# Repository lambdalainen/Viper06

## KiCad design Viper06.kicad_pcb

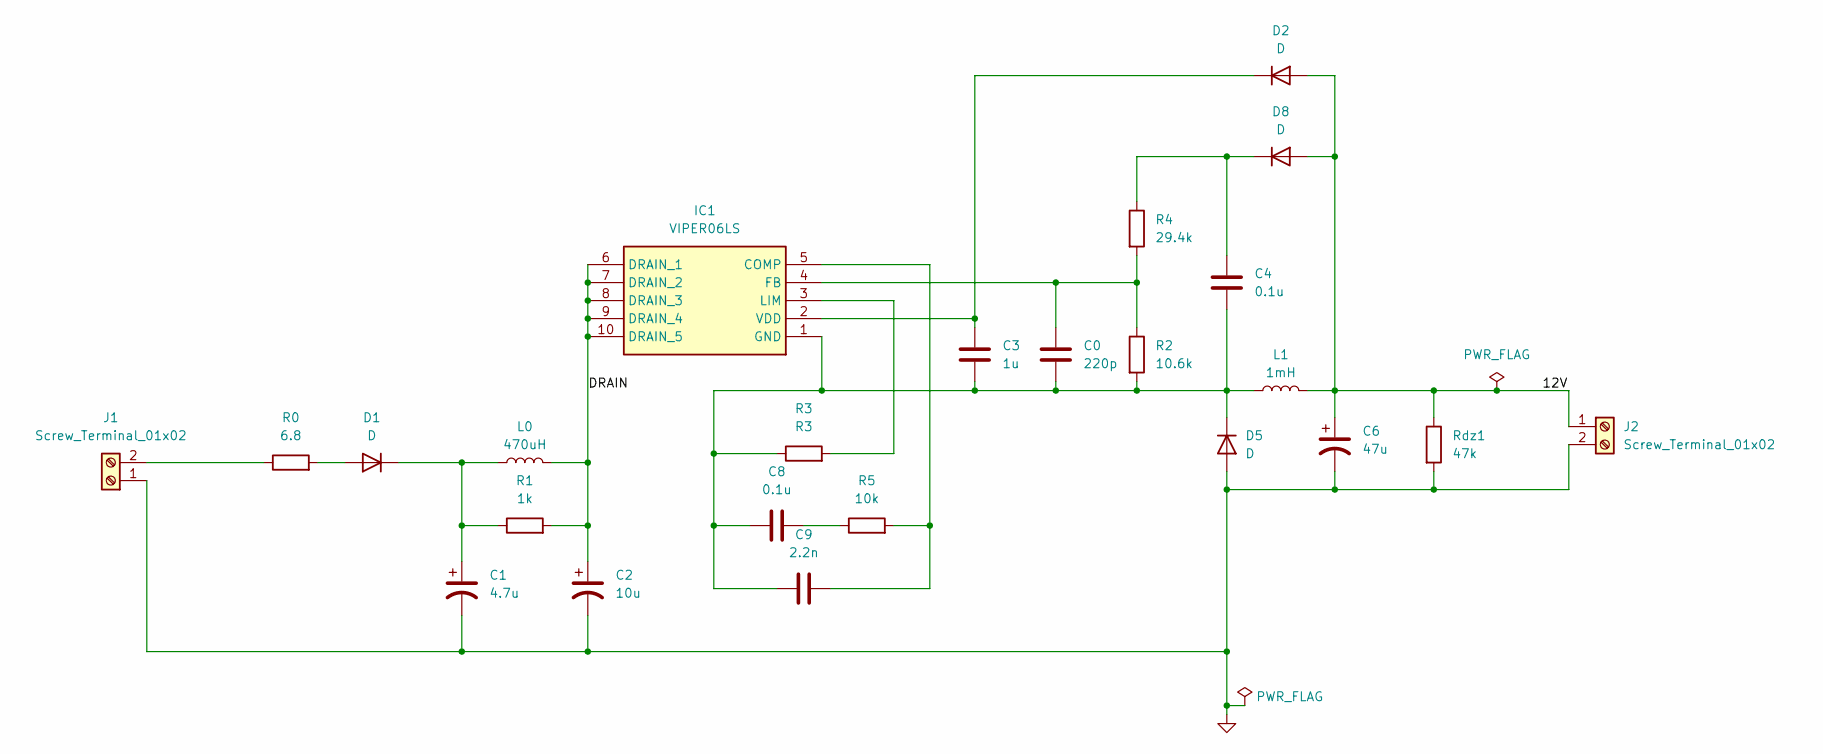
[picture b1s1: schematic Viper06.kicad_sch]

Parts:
C0: 220p; C_0603_1608Metric
C1: 4.7u; CP_Radial_D8.0mm_P3.50mm
C2: 10u; CP_Radial_D10.0mm_P5.00mm
C3: 1u; C_1206_3216Metric
C4, C8: 0.1u; C_0805_2012Metric
C6: 47u; CP_Radial_D6.3mm_P2.50mm
C9: 2.2n; C_0603_1608Metric
D1, D2: D; DIOM5127X229N
D5: D; DIOM5126X265N
D8: D; D_SMA
IC1: VIPER06LS; SOP100P600X175-10N; Manufacturer_Part_Number VIPER06LS; Mouser Part Number 511-VIPER06LS
J1, J2: Screw_Terminal_01x02; TerminalBlock_Phoenix_PT-1,5-2-3.5-H_1x02_P3.50mm_Horizontal
L0: 470uH; L_Axial_L13.0mm_D4.5mm_P5.08mm_Vertical_Fastron_HCCC
L1: 1mH; L_Radial_D7.8mm_P5.00mm_Fastron_07HCP
R0: 6.8; R_Axial_DIN0207_L6.3mm_D2.5mm_P10.16mm_Horizontal
R1: 1k; R_0805_2012Metric
R2: 10.6k; R_0805_2012Metric
R3: R3; R_Axial_DIN0207_L6.3mm_D2.5mm_P10.16mm_Horizontal
R4: 29.4k; R_0805_2012Metric
R5: 10k; R_0805_2012Metric
Rdz1: 47k; R_0805_2012Metric

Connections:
/12V: C6.1, D2.2 (A), D8.2 (A), J2.1, L1.2, Rdz1.1
/DRAIN: C2.1, IC1.6 (DRAIN_1), IC1.7 (DRAIN_2), IC1.8 (DRAIN_3), IC1.9 (DRAIN_4), IC1.10 (DRAIN_5), L0.2, R1.2
GND: C1.2, C2.2, C6.2, D5.2 (A), J1.1, J2.2, Rdz1.2
unnamed: C8.2, R5.1
unnamed: D1.2 (A), R0.2
unnamed: C1.1, D1.1 (K), L0.1, R1.1
unnamed: C3.1, D2.1 (K), IC1.2 (VDD)
unnamed: C0.2, C3.2, C4.2, C8.1, C9.1, D5.1 (K), IC1.1 (GND), L1.1, R2.2, R3.1
unnamed: C4.1, D8.1 (K), R4.1
unnamed: C9.2, IC1.5 (COMP), R5.2
unnamed: C0.1, IC1.4 (FB), R2.1, R4.2
unnamed: IC1.3 (LIM), R3.2
unnamed: J1.2, R0.1

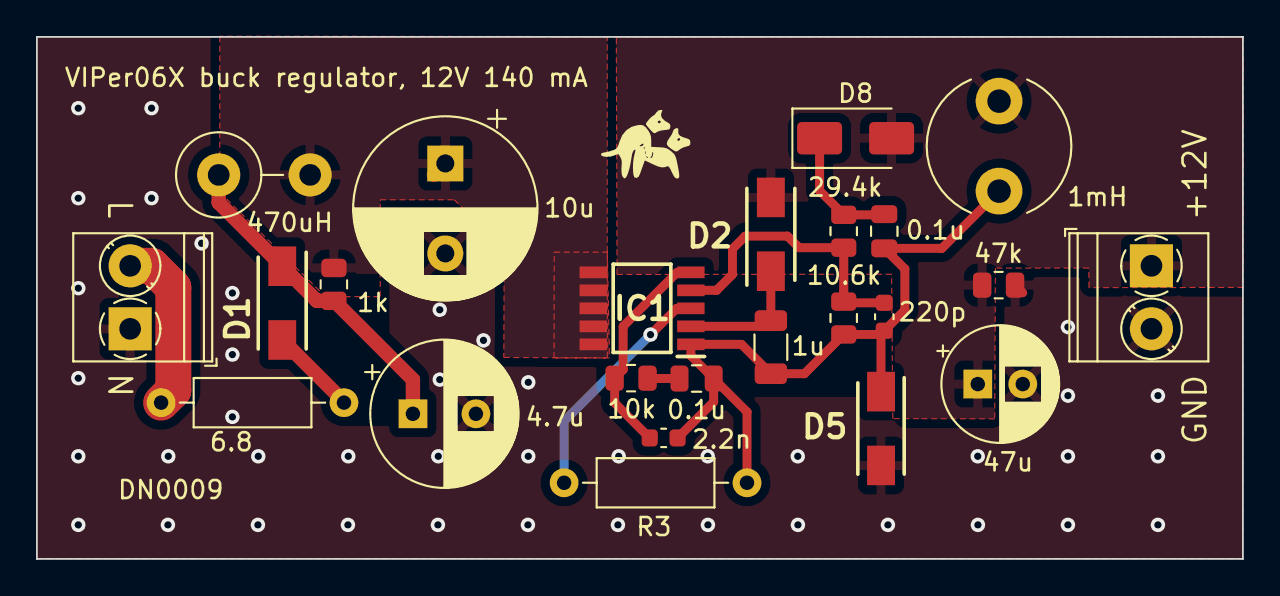
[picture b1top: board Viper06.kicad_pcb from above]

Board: 2 copper layers, 67.0 x 29.0 mm, 24 parts (0 on the bottom side), 13 nets.

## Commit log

2024-02-04 Add VIPER06LS
2024-02-18 Add S1M-E3_61T
    Rectifiers 1.0 Amp 1000 Volt
2024-02-18 Add STTH1L06A
    Rectifiers 1.0 Amp 600 Volt, Fast Recovery Rectifiers
2024-02-19 Add fp-lib-table and sym-lib-table
2024-02-19 Add custom design rules for JLCPCB
2024-02-19 Finish schematics and layout
2024-02-19 Plot Gerber files
2024-03-02 Add comments to schematics
